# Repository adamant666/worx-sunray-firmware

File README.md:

Raspberry Pi4

🧰 Előkészületek

✅ Szükséges eszközök:
•	Raspberry Pi 4 (ajánlott min. 2GB RAM)
•	microSD kártya (legalább 16GB, Class 10)
•	Monitor, billentyűzet az első indításhoz (vagy SSH ha headless)
•	Internet kapcsolat (Ethernet vagy Wi-Fi)
________________________________________
📦 1. Raspbian (Raspberry Pi OS) telepítése
1.	Töltsd le a Raspberry Pi Imager-t:
o	https://www.raspberrypi.com/software
2.	Telepítsd a Raspberry Pi OS Lite verzióját (nincs GUI, kevesebb erőforrás kell):
o	Válaszd a „Raspberry Pi OS Lite (64-bit)” opciót.
o	Flash-eld az SD-kártyára.
3.	SSH engedélyezése (ha headless):
o	A boot partícióba hozz létre egy üres ssh nevű fájlt (touch ssh).
4.	Első indítás után:
•	sudo apt update && sudo apt upgrade
•	sudo apt install git build-essential cmake libi2c-dev i2c-tools

🧠 2. Sunray landrumower-linux projekt letöltése és fordítása
•	git clone -b landrumower-linux https://github.com/EinEinfach/Sunray.git
•	cd Sunray
•	make
Ez lefordítja a fő programot, amiből lesz egy ./sunray bináris.
📁 A src/ mappában található a fő logika, main.cpp a belépési pont.

🧪 3. Futás tesztelése:
./sunray
Ha minden jól megy, kiírja a konzolra a rendszer állapotát, és várja a szenzor/vezérlő csatlakozásokat (pl. UART-on a Pico-tól).

🔌 4. UART kommunikáció engedélyezése (később a Pico-hoz)
A Pi-n a GPIO14 (TX) és GPIO15 (RX) lábakon érkezik majd a soros adat a Pico-tól.
1.	Engedélyezd a hardveres UART-ot:
•	sudo raspi-config
Interfacing Options → Serial 
  		Login shell over serial: No 
  		Enable serial port hardware: Yes

2.	Indítsd újra:

•	sudo reboot

3.	A Pi oldalon a /dev/serial0 (vagy /dev/ttyAMA0) lesz az elérési út.

🧠 5. Raspberry Pi Pico firmware
A pico/ könyvtárban található külön firmware, amit a Pico-ra kell fordítani (külön lépés, CMake-t igényel). Erről tudok külön útmutatót írni.

Pico: 

✅ Pico firmware feltöltése – legegyszerűbb mód
🔌 1. Tedd DFU (bootloader) módba a Pico-t:
1.	Tartsd lenyomva a BOOTSEL gombot.
2.	Miközben nyomva tartod, csatlakoztasd a Pico-t USB-n a számítógéphez.
3.	Engedd el a BOOTSEL gombot.
4.	Meg fog jelenni egy új USB meghajtó pl. RPI-RP2 néven.
5.	https://micropython.org/resources/firmware/RPI_PICO-20241129-v1.24.1.uf2 másold a Pico-ra

📁 2. Töltsd le a firmware-t:
Menj ide:
📂 https://github.com/adamant666/worx/tree/main/landrumower/firmware
➡️ Közvetlen letöltés (jobb klikk + "Mentés másként"):
landrumower/firmware

💾 3. Másold rá a Pico-ra:
Egyszerűen másold rá a .uf2 fájlt az RPI-RP2 meghajtóra, és a Pico automatikusan újraindul az új firmware-rel.

🔁 4. Csatlakoztasd a Raspberry Pi-hez:
•	A Pico most már soros protokollon keresztül kommunikál a Pi-vel.
•	Csatlakoztasd az alábbi GPIO lábakat a Pi és a Pico között:
PI GPIO	FUNKCIÓ	PICO GPIO
GPIO14	TXD	GPIO1 (UART RX)
GPIO15	RXD	GPIO0 (UART TX)
GND	GND	GND
A Pico-n az alapértelmezett UART0 a GPIO 0 (TX) és GPIO 1 (RX) lábakon van.

🧪 Tesztelés:
Indítsd el újra a Sunray-t a Raspberry Pi-n:
•	./sunray
Ha minden jól ment, elindul a kommunikáció a Pico-val, és az állapotlogban látod, hogy érzékeli a mikrokontrollert és olvassa az adatokat (pl. IMU, motor állapot).

TESZT mód

📌 Mit kell módosítani a config.h fájlban a teszt módhoz?
1.	Nyisd meg a fájlt szerkesztésre a Raspberry Pi-n:
•	nano Sunray/landrumower/config.h
//define DRV_SERIAL_ROBOT  1     // Linux (Alfred)
//#define DRV_ARDUMOWER     1   // keep this for Ardumower
#define DRV_SIM_ROBOT     1   // simul
2.	Mentsd el a módosításokat (CTRL + X, Y, Enter).

3.	Fordítsd újra a kódot:

•	make clean
•	make

4.	Indítsd el a Sunray-t teszt módban:

•	./sunray

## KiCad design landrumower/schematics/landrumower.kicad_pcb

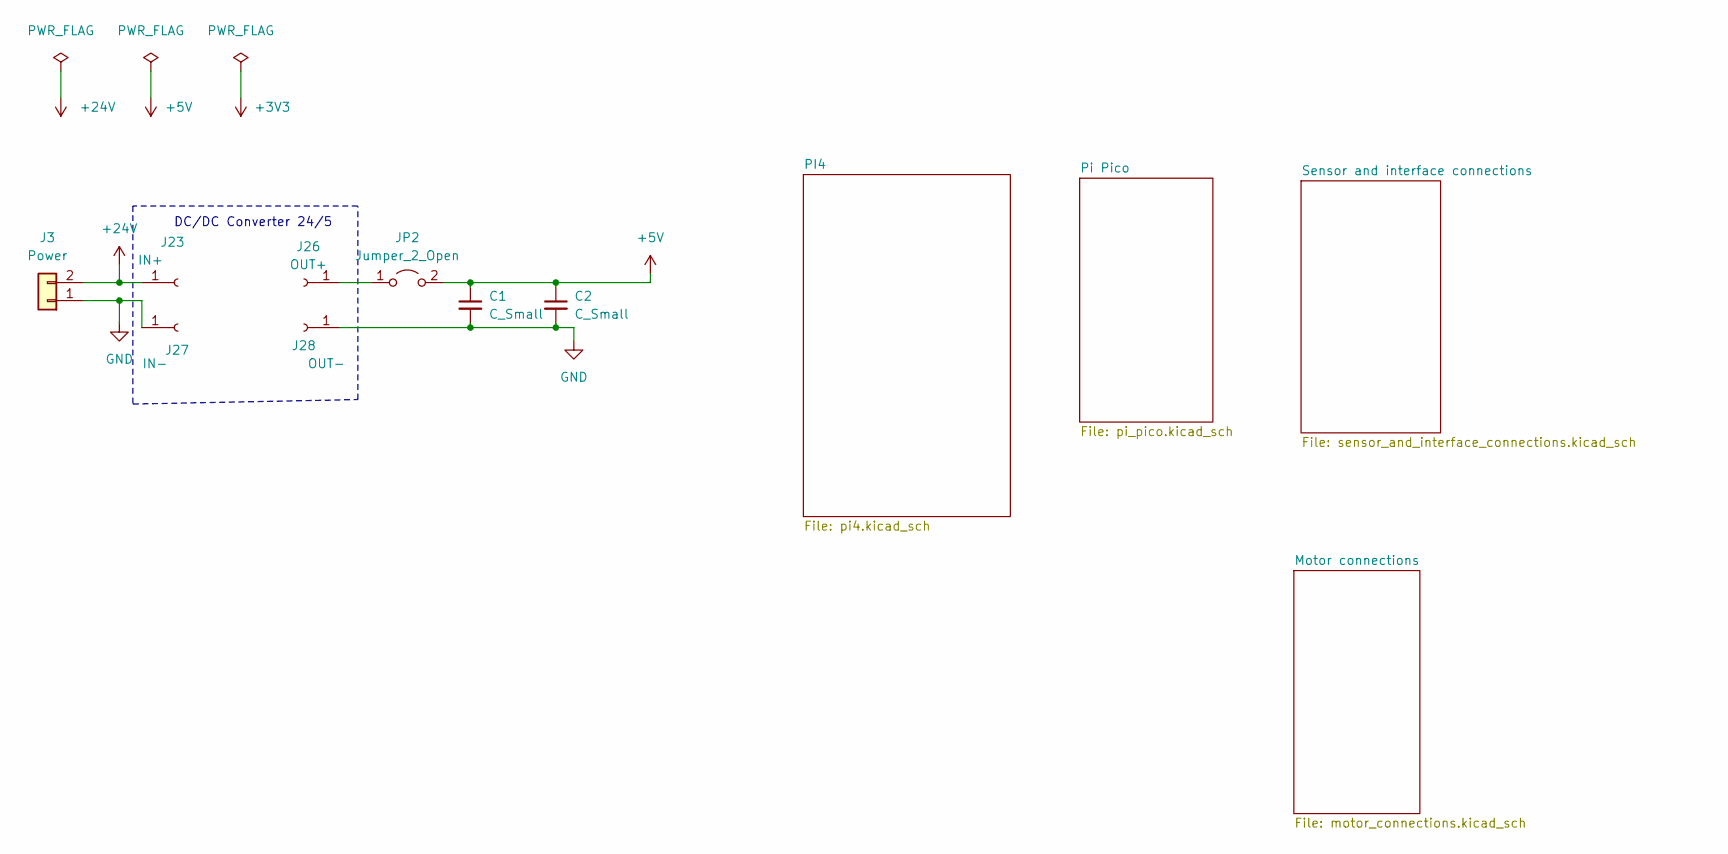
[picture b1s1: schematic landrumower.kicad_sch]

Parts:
C1, C2: C_Small; C_0805_2012Metric_Pad1.18x1.45mm_HandSolder
J3: Power; TerminalBlock_Altech_AK300-2_P5.00mm
J23: IN+; PinSocket_1x01_P2.54mm_Vertical
J26: OUT+; PinSocket_1x01_P2.54mm_Vertical
J27: IN-; PinSocket_1x01_P2.54mm_Vertical
J28: OUT-; PinSocket_1x01_P2.54mm_Vertical
JP2: Jumper_2_Open; SolderJumper-2_P1.3mm_Open_Pad1.0x1.5mm

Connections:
+5V: C1.1, C2.1, JP2.2 (B); also elsewhere on the board
+24V: J3.2, J23.1
GND: C1.2, C2.2, J3.1, J27.1, J28.1; also elsewhere on the board
unnamed: J26.1, JP2.1 (A)

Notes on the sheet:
DC/DC Converter 24/5

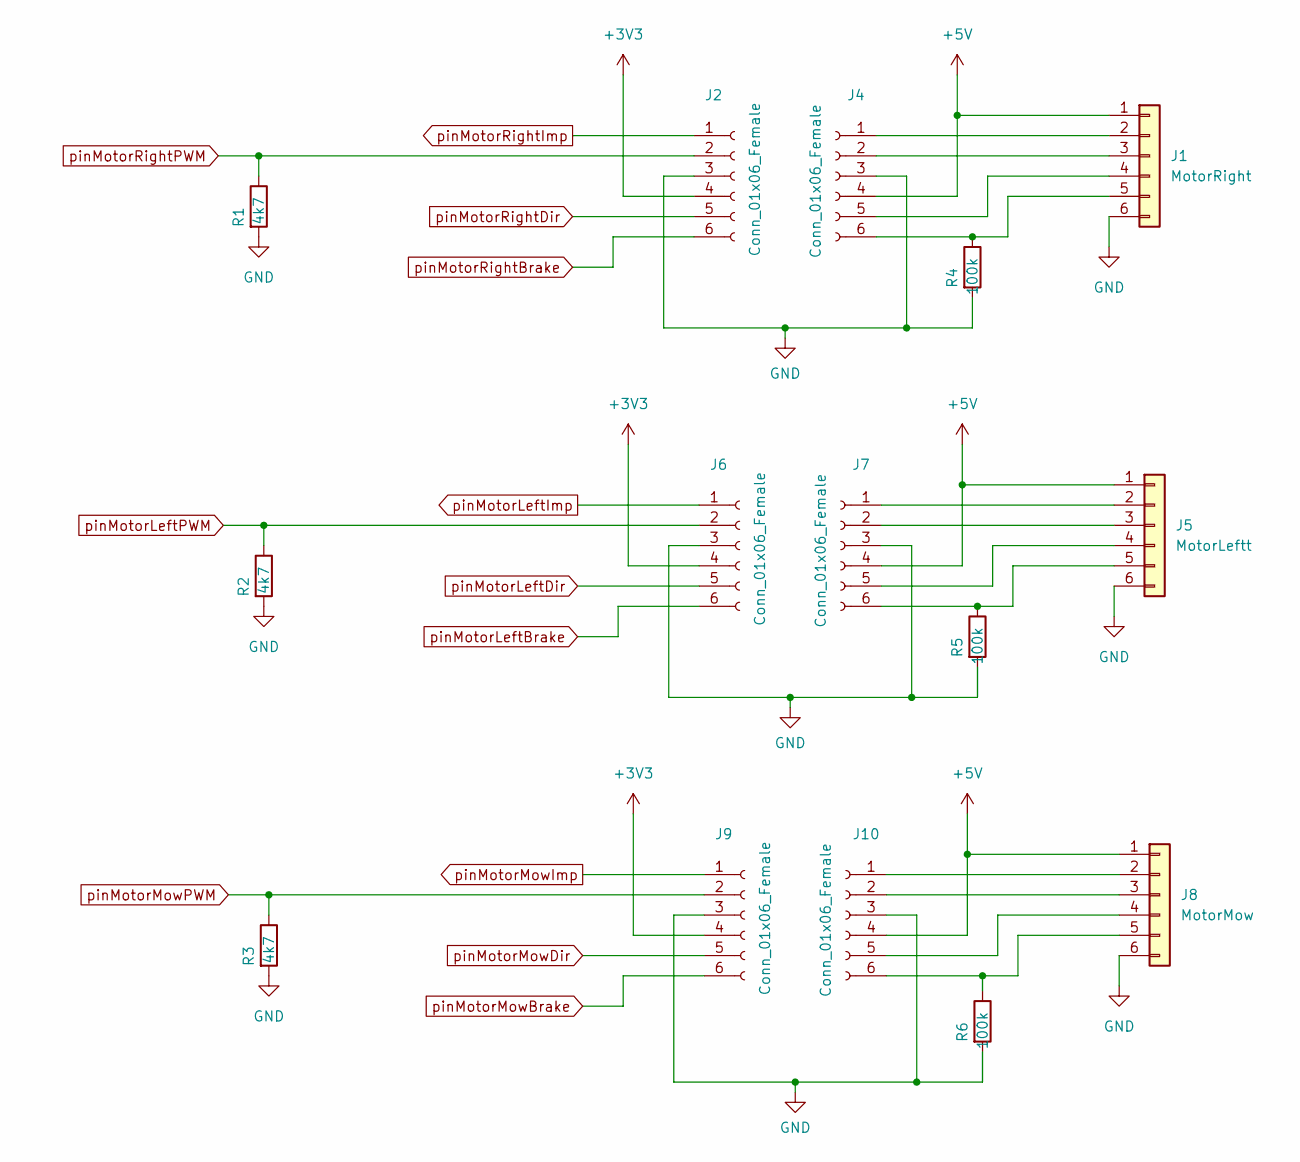
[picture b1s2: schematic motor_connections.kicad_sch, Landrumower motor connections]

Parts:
J1: MotorRight; JST_EH_B6B-EH-A_1x06_P2.50mm_Vertical
J2, J4, J6, J7, J9, J10: Conn_01x06_Female; PinSocket_1x06_P2.54mm_Vertical
J5: MotorLeftt; JST_EH_B6B-EH-A_1x06_P2.50mm_Vertical
J8: MotorMow; JST_EH_B6B-EH-A_1x06_P2.50mm_Vertical
R1, R2, R3: 4k7; R_0805_2012Metric_Pad1.20x1.40mm_HandSolder
R4, R5, R6: 100k; R_0805_2012Metric_Pad1.20x1.40mm_HandSolder

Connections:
+3V3: J2.4, J6.4, J9.4; also elsewhere on the board
+5V: J1.1, J4.4, J5.1, J7.4, J8.1, J10.4; also elsewhere on the board
GND: J1.6, J2.3, J4.3, J5.6, J6.3, J7.3, J8.6, J9.3, J10.3, R1.2, R2.2, R3.2, R4.2, R5.2, R6.2; also elsewhere on the board
unnamed: J1.2, J4.1
unnamed: J1.3, J4.2
unnamed: J1.4, J4.5
unnamed: J1.5, J4.6, R4.1
unnamed: J5.2, J7.1
unnamed: J5.3, J7.2
unnamed: J5.4, J7.5
unnamed: J5.5, J7.6, R5.1
unnamed: J8.2, J10.1
unnamed: J8.3, J10.2
unnamed: J8.4, J10.5
unnamed: J8.5, J10.6, R6.1
pinMotorLeftBrake: J6.6; also elsewhere on the board
pinMotorLeftDir: J6.5; also elsewhere on the board
pinMotorLeftImp: J6.1; also elsewhere on the board
pinMotorLeftPWM: J6.2, R2.1; also elsewhere on the board
pinMotorMowBrake: J9.6; also elsewhere on the board
pinMotorMowDir: J9.5; also elsewhere on the board
pinMotorMowImp: J9.1; also elsewhere on the board
pinMotorMowPWM: J9.2, R3.1; also elsewhere on the board
pinMotorRightBrake: J2.6; also elsewhere on the board
pinMotorRightDir: J2.5; also elsewhere on the board
pinMotorRightImp: J2.1; also elsewhere on the board
pinMotorRightPWM: J2.2, R1.1; also elsewhere on the board

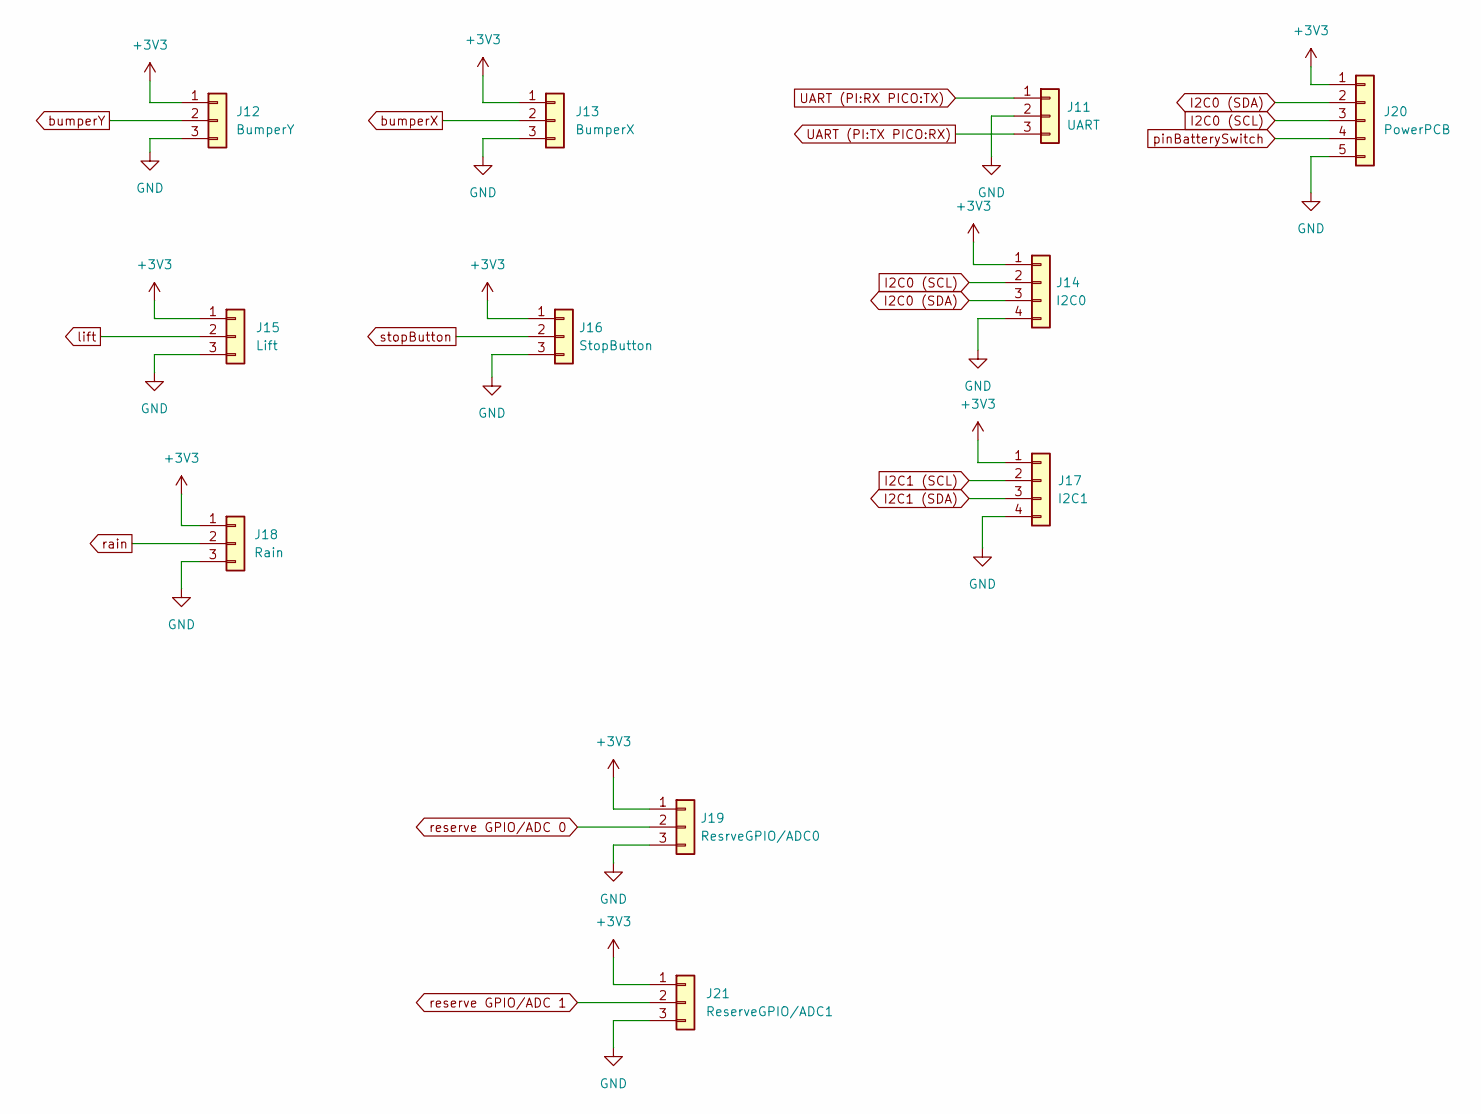
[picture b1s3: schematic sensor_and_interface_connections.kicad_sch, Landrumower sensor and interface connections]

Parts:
J11: UART; JST_EH_B3B-EH-A_1x03_P2.50mm_Vertical
J12: BumperY; JST_EH_B3B-EH-A_1x03_P2.50mm_Vertical
J13: BumperX; JST_EH_B3B-EH-A_1x03_P2.50mm_Vertical
J14: I2C0; JST_EH_B4B-EH-A_1x04_P2.50mm_Vertical
J15: Lift; JST_EH_B3B-EH-A_1x03_P2.50mm_Vertical
J16: StopButton; JST_EH_B3B-EH-A_1x03_P2.50mm_Vertical
J17: I2C1; JST_EH_B4B-EH-A_1x04_P2.50mm_Vertical
J18: Rain; JST_EH_B3B-EH-A_1x03_P2.50mm_Vertical
J19: ResrveGPIO/ADC0; JST_EH_B3B-EH-A_1x03_P2.50mm_Vertical
J20: PowerPCB; JST_EH_B5B-EH-A_1x05_P2.50mm_Vertical
J21: ReserveGPIO/ADC1; JST_EH_B3B-EH-A_1x03_P2.50mm_Vertical

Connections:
+3V3: J12.1, J13.1, J14.1, J15.1, J16.1, J17.1, J18.1, J19.1, J20.1, J21.1; also elsewhere on the board
GND: J11.2, J12.3, J13.3, J14.4, J15.3, J16.3, J17.4, J18.3, J19.3, J20.5, J21.3; also elsewhere on the board
I2C0 (SCL): J14.2, J20.3; also elsewhere on the board
I2C0 (SDA): J14.3, J20.2; also elsewhere on the board
I2C1 (SCL): J17.2; also elsewhere on the board
I2C1 (SDA): J17.3; also elsewhere on the board
UART (PI:RX PICO:TX): J11.1; also elsewhere on the board
UART (PI:TX PICO:RX): J11.3; also elsewhere on the board
bumperX: J13.2; also elsewhere on the board
bumperY: J12.2; also elsewhere on the board
lift: J15.2; also elsewhere on the board
pinBatterySwitch: J20.4; also elsewhere on the board
rain: J18.2; also elsewhere on the board
reserve GPIO/ADC 0: J19.2; also elsewhere on the board
reserve GPIO/ADC 1: J21.2; also elsewhere on the board
stopButton: J16.2; also elsewhere on the board

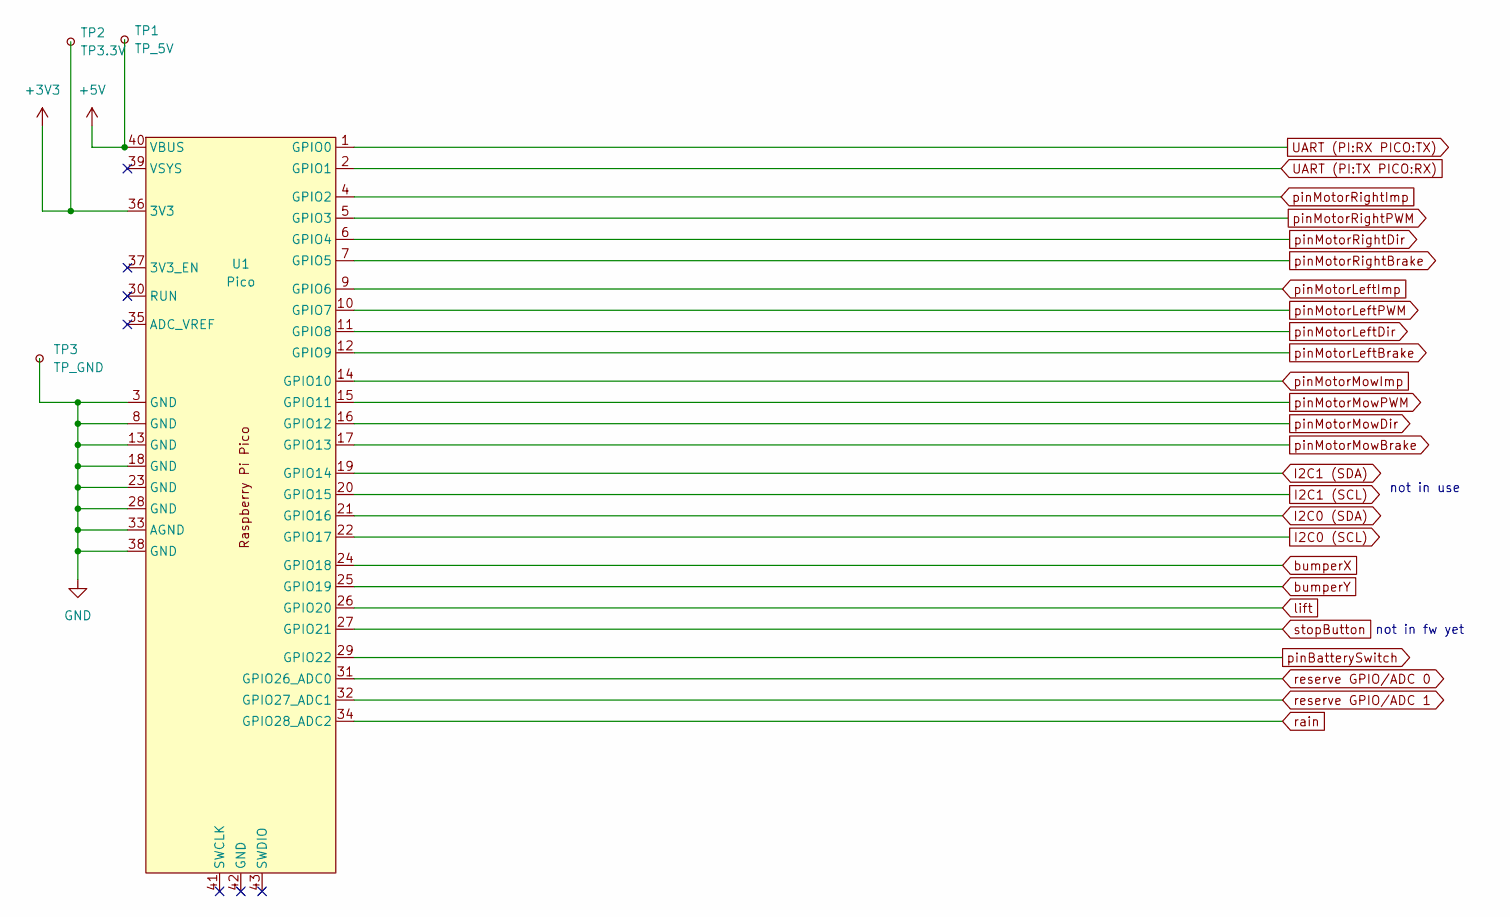
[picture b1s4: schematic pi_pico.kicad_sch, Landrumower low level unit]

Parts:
TP1: TP_5V; TestPoint_Pad_D2.0mm
TP2: TP3.3V; TestPoint_Pad_D2.0mm
TP3: TP_GND; TestPoint_Pad_D2.0mm
U1: Pico; RPi_Pico_SMD_TH

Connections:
+3V3: TP2.1, U1.36 (3V3); also elsewhere on the board
+5V: TP1.1, U1.40 (VBUS); also elsewhere on the board
GND: TP3.1, U1.3 (GND), U1.8 (GND), U1.13 (GND), U1.18 (GND), U1.23 (GND), U1.28 (GND), U1.33 (AGND), U1.38 (GND); also elsewhere on the board
I2C0 (SCL): U1.22 (GPIO17); also elsewhere on the board
I2C0 (SDA): U1.21 (GPIO16); also elsewhere on the board
I2C1 (SCL): U1.20 (GPIO15); also elsewhere on the board
I2C1 (SDA): U1.19 (GPIO14); also elsewhere on the board
UART (PI:RX PICO:TX): U1.1 (GPIO0); also elsewhere on the board
UART (PI:TX PICO:RX): U1.2 (GPIO1); also elsewhere on the board
bumperX: U1.24 (GPIO18); also elsewhere on the board
bumperY: U1.25 (GPIO19); also elsewhere on the board
lift: U1.26 (GPIO20); also elsewhere on the board
pinBatterySwitch: U1.29 (GPIO22); also elsewhere on the board
pinMotorLeftBrake: U1.12 (GPIO9); also elsewhere on the board
pinMotorLeftDir: U1.11 (GPIO8); also elsewhere on the board
pinMotorLeftImp: U1.9 (GPIO6); also elsewhere on the board
pinMotorLeftPWM: U1.10 (GPIO7); also elsewhere on the board
pinMotorMowBrake: U1.17 (GPIO13); also elsewhere on the board
pinMotorMowDir: U1.16 (GPIO12); also elsewhere on the board
pinMotorMowImp: U1.14 (GPIO10); also elsewhere on the board
pinMotorMowPWM: U1.15 (GPIO11); also elsewhere on the board
pinMotorRightBrake: U1.7 (GPIO5); also elsewhere on the board
pinMotorRightDir: U1.6 (GPIO4); also elsewhere on the board
pinMotorRightImp: U1.4 (GPIO2); also elsewhere on the board
pinMotorRightPWM: U1.5 (GPIO3); also elsewhere on the board
rain: U1.34 (GPIO28_ADC2); also elsewhere on the board
reserve GPIO/ADC 0: U1.31 (GPIO26_ADC0); also elsewhere on the board
reserve GPIO/ADC 1: U1.32 (GPIO27_ADC1); also elsewhere on the board
stopButton: U1.27 (GPIO21); also elsewhere on the board

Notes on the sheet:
not in use
not in fw yet

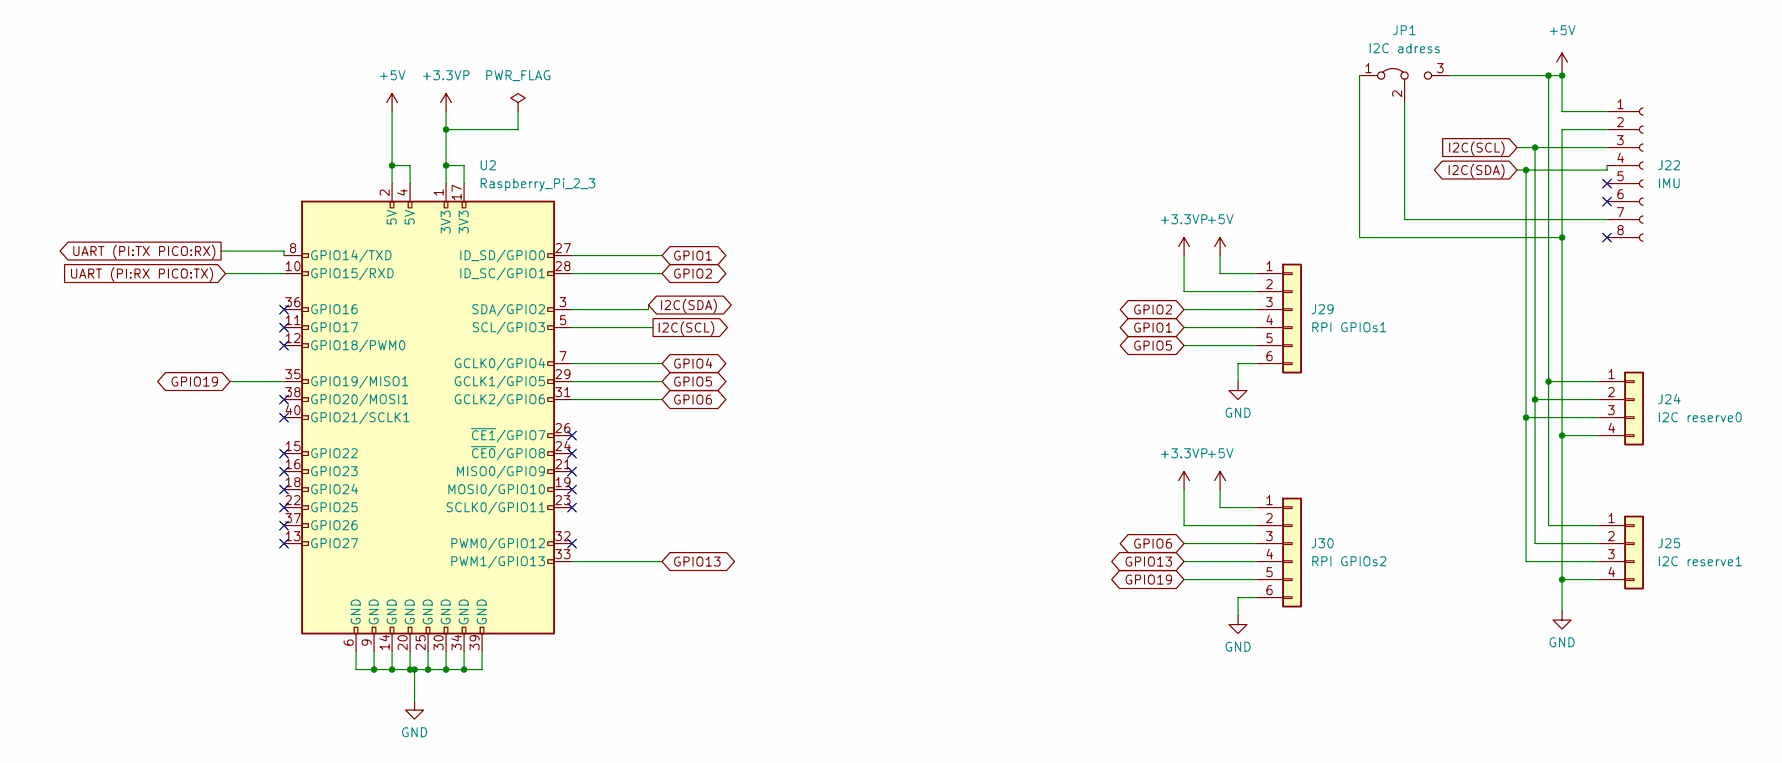
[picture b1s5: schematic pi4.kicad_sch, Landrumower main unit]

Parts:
J22: IMU; PinSocket_1x08_P2.54mm_Vertical
J24: I2C reserve0; JST_EH_B4B-EH-A_1x04_P2.50mm_Vertical
J25: I2C reserve1; JST_EH_B4B-EH-A_1x04_P2.50mm_Vertical
J29: RPI GPIOs1; JST_EH_B6B-EH-A_1x06_P2.50mm_Vertical
J30: RPI GPIOs2; JST_EH_B6B-EH-A_1x06_P2.50mm_Vertical
JP1: I2C adress; PinHeader_1x03_P2.54mm_Vertical
U2: Raspberry_Pi_2_3; PinSocket_2x20_P2.54mm_Vertical

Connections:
+3.3VP: J29.2, J30.2, U2.1 (3V3), U2.17 (3V3)
+5V: J22.1, J24.1, J25.1, J29.1, J30.1, JP1.3 (B), U2.2 (5V), U2.4 (5V); also elsewhere on the board
GND: J22.2, J24.4, J25.4, J29.6, J30.6, JP1.1 (A), U2.6 (GND), U2.9 (GND), U2.14 (GND), U2.20 (GND), U2.25 (GND), U2.30 (GND), U2.34 (GND), U2.39 (GND); also elsewhere on the board
GPIO1: J29.4, U2.27 (ID_SD/GPIO0)
GPIO2: J29.3, U2.28 (ID_SC/GPIO1)
GPIO4: U2.7 (GCLK0/GPIO4)
GPIO5: J29.5, U2.29 (GCLK1/GPIO5)
GPIO6: J30.3, U2.31 (GCLK2/GPIO6)
GPIO13: J30.4, U2.33 (PWM1/GPIO13)
GPIO19: J30.5, U2.35 (GPIO19/MISO1)
I2C(SCL): J22.3, J24.2, J25.2, U2.5 (SCL/GPIO3)
I2C(SDA): J22.4, J24.3, J25.3, U2.3 (SDA/GPIO2)
unnamed: J22.7, JP1.2 (C)
UART (PI:RX PICO:TX): U2.10 (GPIO15/RXD); also elsewhere on the board
UART (PI:TX PICO:RX): U2.8 (GPIO14/TXD); also elsewhere on the board

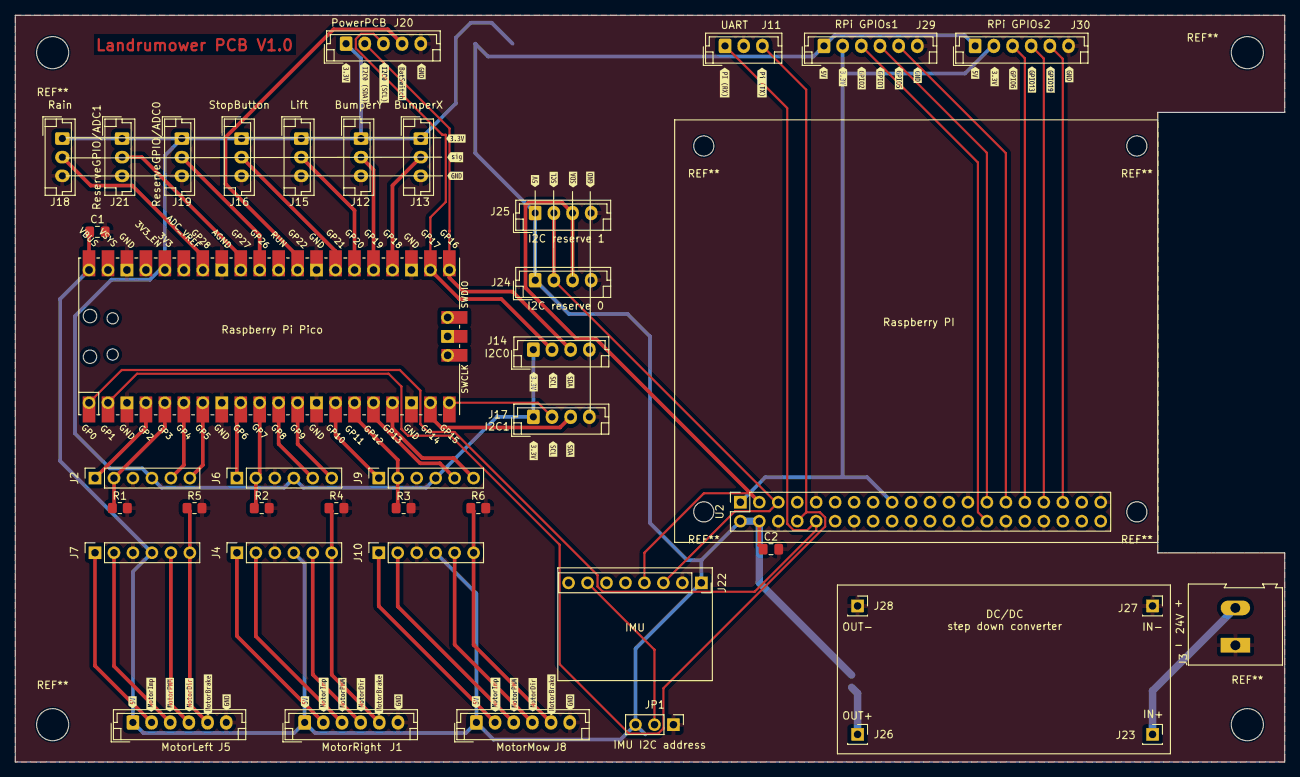
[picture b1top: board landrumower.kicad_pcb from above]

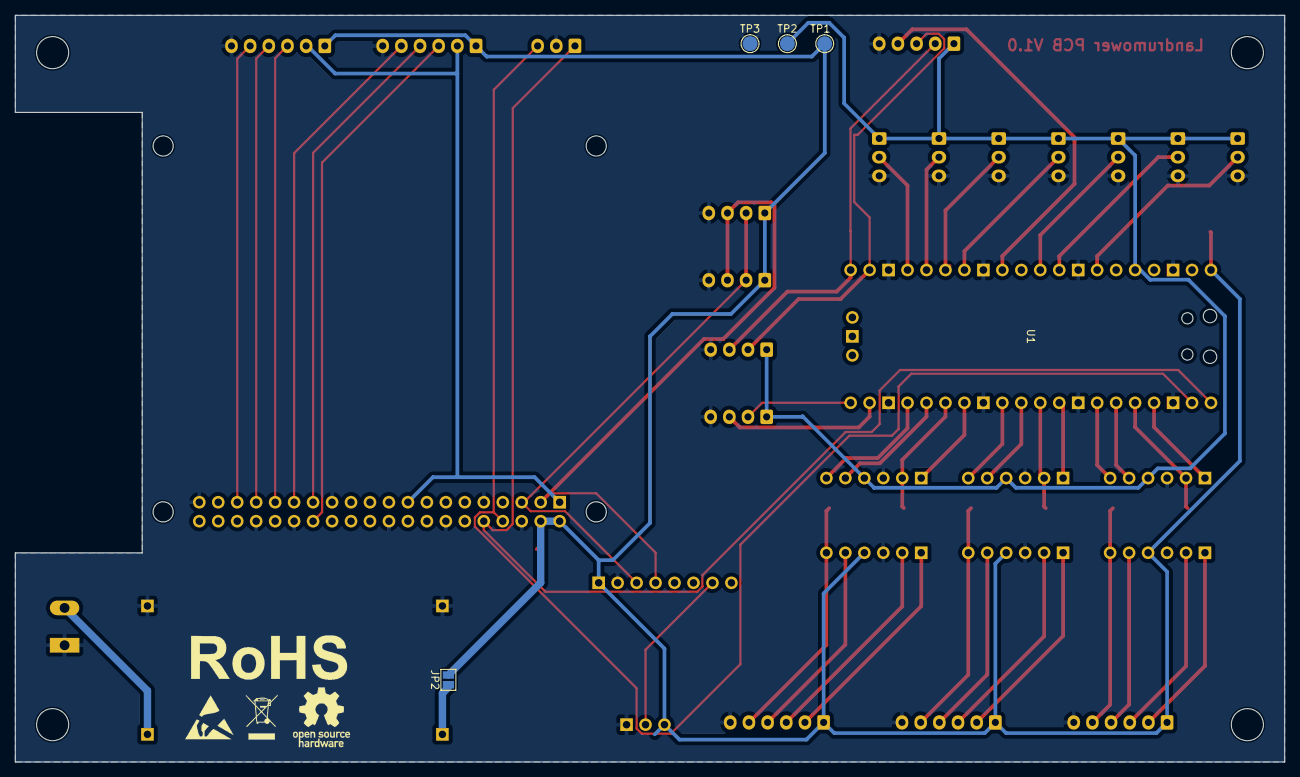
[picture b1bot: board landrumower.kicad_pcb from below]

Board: 2 copper layers, 170.0 x 100.0 mm, 95 parts (4 on the bottom side), 53 nets.

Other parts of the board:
kibuzzard-65CA0A7B, kibuzzard-65CA0A7B#2, kibuzzard-65CA0A7B#3: G***; kibuzzard-65CA0A7B
kibuzzard-65CA0AF1, kibuzzard-65CA0AF1#2, kibuzzard-65CA0AF1#3: G***; kibuzzard-65CA0AF1
kibuzzard-65CA0B61, kibuzzard-65CA0B61#2: G***; kibuzzard-65CA0B61
kibuzzard-65CA0BDD: G***; kibuzzard-65CA0BDD
kibuzzard-65CA0BE5, kibuzzard-65CA0BE5#2, kibuzzard-65CA0BE5#3: G***; kibuzzard-65CA0BE5
kibuzzard-65CA0CDE, kibuzzard-65CA0CDE#2, kibuzzard-65CA0CDE#3: G***; kibuzzard-65CA0CDE
kibuzzard-65CA0D25, kibuzzard-65CA0D25#2, kibuzzard-65CA0D25#3: G***; kibuzzard-65CA0D25
kibuzzard-65CA1A09: G***; kibuzzard-65CA1A09
kibuzzard-65CA13E2: G***; kibuzzard-65CA13E2
kibuzzard-65CA15BA: G***; kibuzzard-65CA15BA
kibuzzard-65CA15CC: G***; kibuzzard-65CA15CC
kibuzzard-65CA15DA: G***; kibuzzard-65CA15DA
kibuzzard-65CA18B9, kibuzzard-65CA18B9#2: G***; kibuzzard-65CA18B9
kibuzzard-65CA18EE, kibuzzard-65CA18EE#2: G***; kibuzzard-65CA18EE
kibuzzard-65CA19E7: G***; kibuzzard-65CA19E7
kibuzzard-65CA19F9: G***; kibuzzard-65CA19F9
kibuzzard-65CA34CF: G***; kibuzzard-65CA34CF
kibuzzard-65CA34D8: G***; kibuzzard-65CA34D8
kibuzzard-65CA36D0: G***; kibuzzard-65CA36D0
kibuzzard-65CA137E, kibuzzard-65CA137E#2, kibuzzard-65CA137E#3: G***; kibuzzard-65CA137E
kibuzzard-65CA190F: G***; kibuzzard-65CA190F
kibuzzard-65CA191B: G***; kibuzzard-65CA191B
kibuzzard-65CA193C, kibuzzard-65CA193C#2: G***; kibuzzard-65CA193C
kibuzzard-65CA369C: G***; kibuzzard-65CA369C
kibuzzard-65CA1367, kibuzzard-65CA1367#2: G***; kibuzzard-65CA1367
kibuzzard-65CA1392, kibuzzard-65CA1392#2, kibuzzard-65CA1392#3: G***; kibuzzard-65CA1392
kibuzzard-65CA1528: G***; kibuzzard-65CA1528
kibuzzard-65CA1927: G***; kibuzzard-65CA1927
kibuzzard-65CA3687: G***; kibuzzard-65CA3687
kibuzzard-65CA3704: G***; kibuzzard-65CA3704
kibuzzard-65CA3716: G***; kibuzzard-65CA3716

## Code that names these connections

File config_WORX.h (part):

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#define ENABLE_LIFT_DETECTION  1
// should the lift sensor be used for obstacle avoidance (if not, mower will simply turn off cutter motor if lifted)
#define LIFT_OBSTACLE_AVOIDANCE 1  
#define LIFT_INVERT  false       // invert lift sensor state? 

// ------- SD card map load/resume and logging ---------------------------------
// all serial console output can be logged to a (FAT32 formatted) SD card
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#define SONAR_RIGHT_OBSTACLE_CM  10      // stop mowing operation below this distance (cm) 

// ------ rain sensor ----------------------------------------------------------
#define RAIN_ENABLE true                 // if activated, mower will dock when rain sensor triggers
//#define RAIN_ENABLE false

// ------ time-of-flight distance sensor (VL53L0X) -----------------------------
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  // ...
#else
  #define pinMotorEnable  37         // EN motors enable
  #define pinMotorLeftPWM 5          // M1_IN1 left motor PWM pin
  #define pinMotorLeftDir 31         // M1_IN2 left motor Dir pin
  #define pinMotorLeftSense A1       // M1_FB  left motor current sense
  #define pinMotorLeftFault 25       // M1_SF  left motor fault
                                                              
  #define pinMotorRightPWM  3        // M2_IN1 right motor PWM pin
  #define pinMotorRightDir 33        // M2_IN2 right motor Dir pin
  #define pinMotorRightSense A0      // M2_FB  right motor current sense
  #define pinMotorRightFault 27      // M2_SF  right motor fault
                                      
  #define pinMotorMowPWM 2           // M1_IN1 mower motor PWM pin (if using MOSFET, use this pin)
  #define pinMotorMowDir 29          // M1_IN2 mower motor Dir pin (if using MOSFET, keep unconnected)
  #define pinMotorMowSense A3        // M1_FB  mower motor current sense  
  #define pinMotorMowFault 26        // M1_SF  mower motor fault   (if using MOSFET/L298N, keep unconnected)
  #define pinMotorMowEnable 28       // EN mower motor enable      (if using MOSFET/L298N, keep unconnected)
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  #define pinLED 13                  // LED
  #define pinBuzzer 53               // Buzzer
  //#define pinTilt 35                 // Tilt sensor (required for TC-G158 board)
  #define pinLift 35                 // Lift sensor (marked as 'Tilt' on PCB1.3/1.4) 
  #define pinButton 51               // digital ON/OFF button
  #define pinBatteryVoltage A2       // battery voltage sensor
  #define pinBatterySwitch 4         // battery-OFF switch   
  #define pinChargeVoltage A9        // charging voltage sensor
  #define pinChargeCurrent A8        // charge current sensor
  #define pinChargeRelay 50          // charge relay
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  #define pinUserSwitch1 46          // user-defined switch 1
  #define pinUserSwitch2 47          // user-defined switch 2
  #define pinUserSwitch3 48          // user-defined switch 3
  #define pinRain 44                 // rain sensor
  #define pinReservedP14 A7          // reserved
  #define pinReservedP22 A6          // reserved
  #define pinReservedP26 A10         // reserved
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
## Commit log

2025-03-21 README.md
2025-04-03 alfred

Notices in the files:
config_WORX.h:
Copyright (c) 2013-2020 by Alexander Grau, Grau GmbH
Licensed GPLv3 for open source use
